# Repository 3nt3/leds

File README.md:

# leds

LED-controller for my room

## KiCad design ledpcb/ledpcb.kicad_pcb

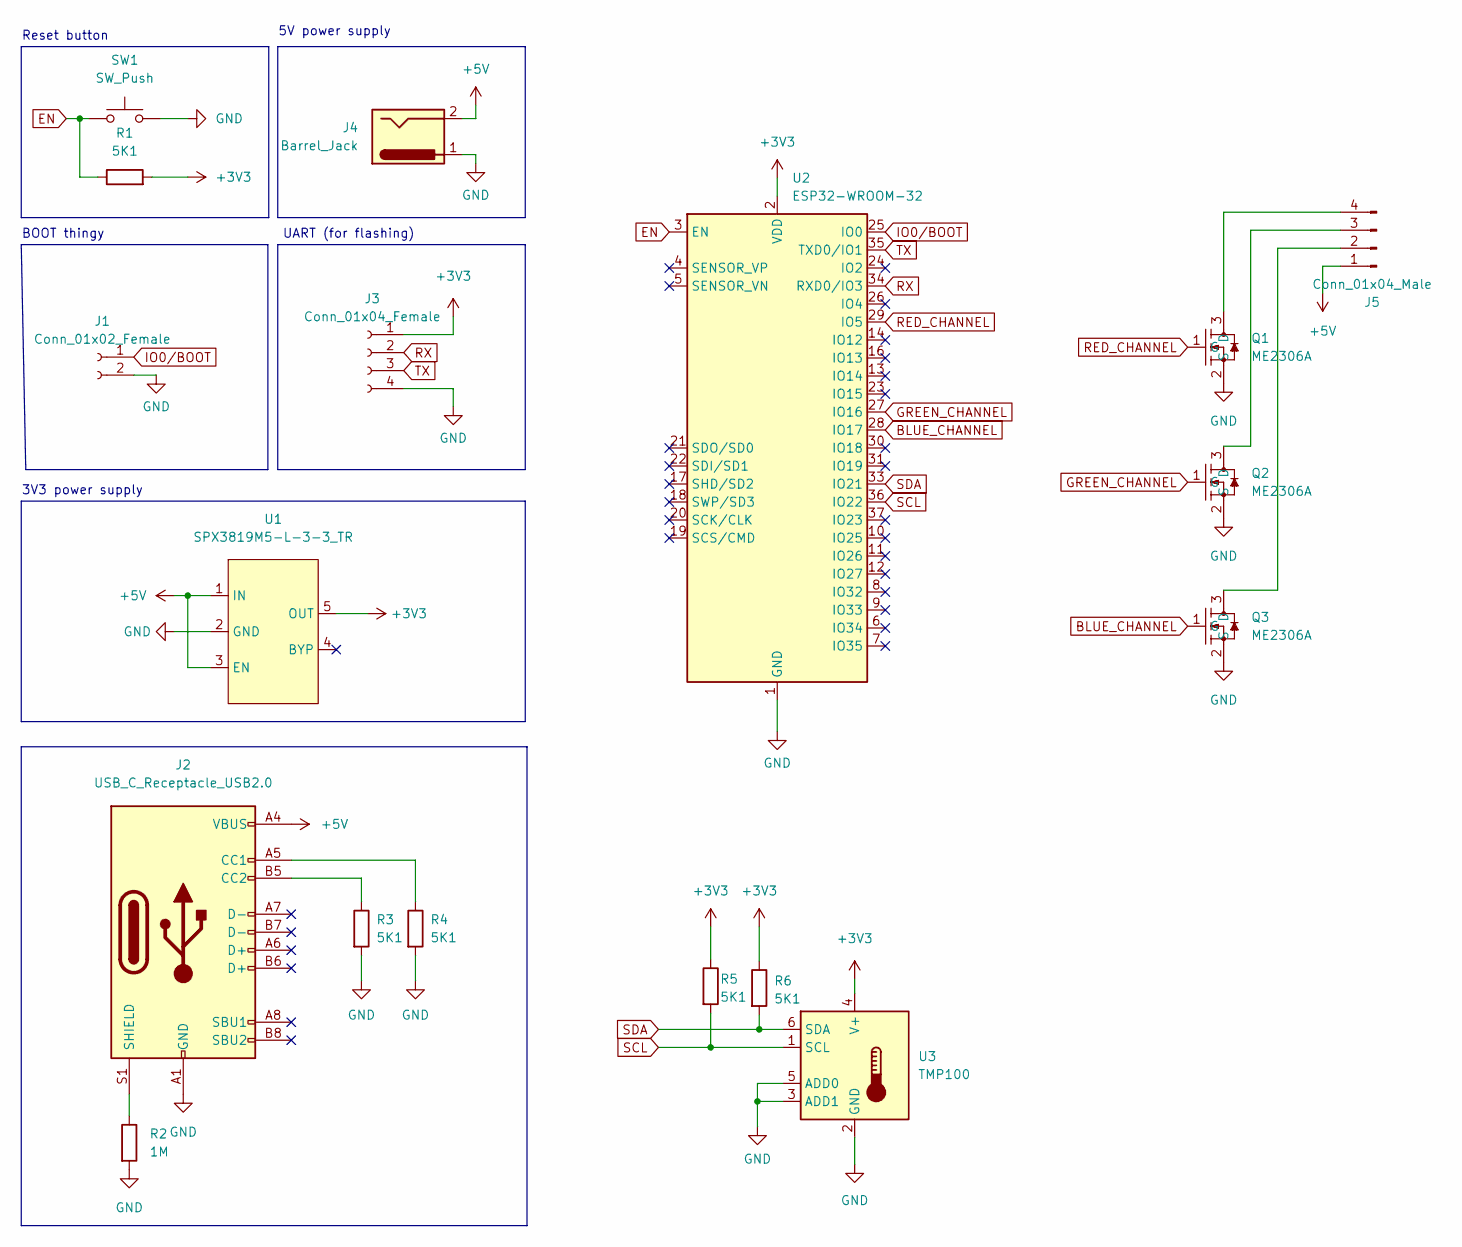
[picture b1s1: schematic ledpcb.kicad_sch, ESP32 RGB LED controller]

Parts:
J1: Conn_01x02_Female; PinHeader_1x02_P2.00mm_Vertical
J2: USB_C_Receptacle_USB2.0; USB_C_Receptacle_Palconn_UTC16-G
J3: Conn_01x04_Female; PinHeader_1x04_P2.00mm_Horizontal
J4: Barrel_Jack; DEALON DC-S050-200
J5: Conn_01x04_Male; PinHeader_1x04_P2.00mm_Horizontal
Q1, Q2, Q3: ME2306A; SOT-23_L2.9-W1.3-P1.90-LS2.4-BR; LCSC Part C165219
R1, R3, R4, R5, R6: 5K1; R_0603_1608Metric_Pad0.98x0.95mm_HandSolder
R2: 1M; R_2512_6332Metric_Pad1.40x3.35mm_HandSolder
SW1: SW_Push; KEY-SMD_4P-L6.2-W6.5-P4.50-LS8.0_SKHMXX
U1: SPX3819M5-L-3-3_TR; SOT-23-5_L3.0-W1.7-P0.95-LS2.8-BR; LCSC Part C9055
U2: ESP32-WROOM-32
U3: TMP100; SOT-23-6

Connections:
+3V3: J3.1, R1.2, R5.1, R6.1, U1.5 (OUT), U2.2 (VDD), U3.4 (V+)
+5V: J2.A4 (VBUS), J2.A9 (VBUS), J2.B4 (VBUS), J2.B9 (VBUS), J4.2, J5.1, U1.1 (IN), U1.3 (EN)
BLUE_CHANNEL: Q3.1 (G), U2.28 (IO17)
EN: R1.1, SW1.1, U2.3 (EN)
GND: J1.2, J2.A1 (GND), J2.A12 (GND), J2.B1 (GND), J2.B12 (GND), J3.4, J4.1, Q1.2 (S), Q2.2 (S), Q3.2 (S), R2.2, R3.2, R4.2, SW1.2, U1.2 (GND), U2.1 (GND), U2.15 (GND), U2.38 (GND), U2.39 (GND), U3.2 (GND), U3.3 (ADD1), U3.5 (ADD0)
GREEN_CHANNEL: Q2.1 (G), U2.27 (IO16)
IO0/BOOT: J1.1, U2.25 (IO0)
unnamed: J2.A5 (CC1), R4.1
unnamed: J2.B5 (CC2), R3.1
unnamed: J2.S1 (SHIELD), R2.1
unnamed: J5.2, Q3.3 (D)
unnamed: J5.3, Q2.3 (D)
unnamed: J5.4, Q1.3 (D)
RED_CHANNEL: Q1.1 (G), U2.29 (IO5)
RX: J3.2, U2.34 (RXD0/IO3)
SCL: R5.2, U2.36 (IO22), U3.1 (SCL)
SDA: R6.2, U2.33 (IO21), U3.6 (SDA)
TX: J3.3, U2.35 (TXD0/IO1)

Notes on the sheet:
3V3 power supply
UART (for flashing)
5V power supply
Reset button
BOOT thingy

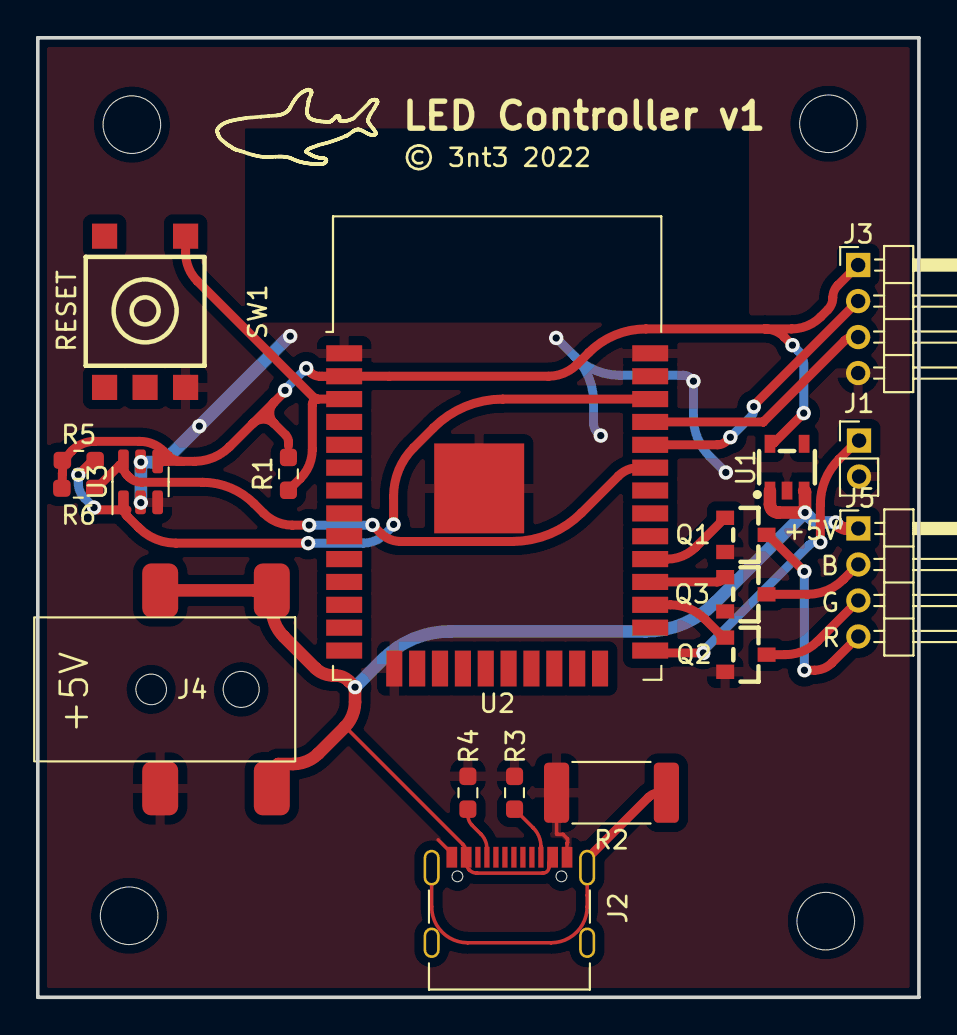
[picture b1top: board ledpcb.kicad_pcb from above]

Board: 2 copper layers, 49.0 x 53.3 mm, 18 parts (0 on the bottom side), 18 nets.

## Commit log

2022-09-15 version
2022-09-16 progress
2022-09-17 add usb c receptable
2022-09-17 fix traces or something
2022-09-29 final?
2022-09-30 add esp-idf template
2022-09-30 whatever
2022-09-30 add readme
2022-09-30 blink an led
2022-09-30 blink two leds
2022-10-01 quicksave so i dont lose progress xD
2022-10-08 do things
2022-10-08 abstract everything to be more good
2022-10-08 things
2022-10-21 use esp32-s3

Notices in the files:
ledpcb/ledpcb.kicad_pcb:
© 3nt3 2022
